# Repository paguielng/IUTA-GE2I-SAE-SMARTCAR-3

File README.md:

# ST STM32: development platform for [PlatformIO](https://platformio.org)

1 Présentation du projet
   ---
1.1 Contexte
   ---
Une entreprise de jouet souhaite développer une voiture pilotée par smartphone, qui intègre plusieurs fonctionnalités comme l'anticollision, le signalement d'obstacle ……

1.2 Objectifs
---
Concevoir, vérifier et valider l'électronique et la programmation d'une voiture pilotée par smartphone afin de :
- Permettre le pilotage de la voiture à partir d'un joystick virtuel sur un smartphone
- Donner, à ce véhicule, de l’autonomie dans certaines prises de décision (anticollision)
- Fournir des informations visuelles et sonores au pilote

1.3 Description de l’existant
---
La voiture est une voiture Radio Commandée déjà existante au catalogue de l'entreprise. Toute l'électronique existante a été supprimée, tout le reste est conservé (carcasse, roues, moteurs, phares …). Les éléments suivants ont été ajoutés à l'intérieur :
- Un module pont en H de référence LF298 pour alimenter le moteur de direction et le moteur de propulsion dans les 2 sens de marche
- Un buzzer passif pour générer un signal avertisseur d'obstacle ou le klaxon
- Deux capteurs infrarouges Sharp de détection d'obstacle
- 6 accumulateurs AA NiMh de 1.2V et 2300mAh en série ou 1 pack batterie de 2 accumulateurs 18650 Li ion de 3.7V de 2600mAh.

1.4 Critères d’acceptabilité du projet
---
Le chef d'entreprise souhaite qu'à la fin de l'étude, lui soient fournis :
- Un dossier de fabrication de la carte électronique (cahier de fabrication + fichiers GERBER + fichier PROTEUS)
- Un dossier technique (cahier de laboratoire + documentation technique + simulations + schémas électriques, schéma d’implantation…)
- Une démonstration avec un prototype opérationnel
- Une étude de coût unitaire pour une production de 100 exemplaires
- Une étude d'autonomie voiture à l’arrêt

2 Expression des besoins
---
2.1 Besoins fonctionnel
---
- Un prototype
- Un dossier technique (cahier de laboratoire)
- Un dossier technique de fabrication (cahier de fabrication ……)
- Une démonstration du système opérationnel

2.2 Fonctionnement global attendu
---
- La voiture est pilotée par smartphone via liaison Bluetooth grâce à un joystick virtuel
- Des dispositifs de sécurité sont mis en œuvre sur la voiture tels que des capteurs de distance d’obstacle avant et arrière, et un avertisseur sonore en fonction de la proximité de l’obstacle.
- L'avertisseur sonore peut être activé directement comme klaxon grâce à un bouton poussoir virtuel sur le smart-phone. Il est aussi possible de générer une mélodie ou des fréquences fixes.
- Un bargraphe virtuel, sur le téléphone, permet d'informer visuellement l'utilisateur de la proximité de l'obstacle à l'avant et/ou du niveau de batterie. (Le niveau de batterie sera indiqué en permanence sauf si proximité d’obs-tacle à l’avant)
- Détection (Près, Moyen et Loin) respectivement moins de 40cm, entre 40 et 60cm et au-delà
- L’utilisateur peut choisir d’activer, de façon permanente, les phares avant et arrière de la voiture grâce à un switch virtuel sur l’écran du smartphone et au besoin de passer dans un mode de gestion automatique grâce à un capteur de luminosité.
- Les phares arrière s’allument plus fort en cas de freinage.
- La température extérieure est reportée sur le smartphone.

2.3 Fonctionnement détaillé attendu
---
- Deux détecteurs de distance infrarouge (un à l’arrière et l’autre à l’avant) permettent de mesurer la distance à l’obstacle et la vitesse d'approche du véhicule, et d’identifier la zone de proximité
- Un buzzer permet d’émettre des bips plus ou moins rapprochés en fonction de la distance à l’obstacle (2 bips par seconde dans la zone Moyen et 4 bips par seconde dans la zone près). Le klaxon est prioritaire sur les bips.
- Le véhicule réduit automatiquement de 50% la consigne de vitesse dans la zone moyenne lorsque le déplace-ment s’effectue vers l’obstacle.
- Le véhicule freine à fond (inversion de la propulsion à consigne maximale), jusqu’à arrêt du véhicule, lorsque le véhicule s’approche de l’obstacle dans la zone près, et cela quel que soit la consigne.
- Les phares arrière s’allument plus fort à chaque freinage.
- Les phares avant et arrière s’allument de façon permanente si le switch virtuel est dans la position “ON” et automatiquement en cas de faible luminosité si le switch est en position “AUTO”
- ,,,,,,,,,,,

3 Contraintes
---
3.1 Coûts
---
Aucune contrainte de coût n’est imposée. En revanche un calcul de coût unitaire pour une production de 100 cartes est attendu (composants électroniques + circuit imprimé + voiture + accessoires + main d'œuvre).

3.2 Autonomie de fonctionnement
---
La voiture doit avoir une autonomie d'au moins 30 minutes avec une batterie de 6 accumulateurs NiMh de capacité 2300mAh.

3.3 Délais de réalisation
---
2h C / 28h TD / 27h TP / 25h autonomie

4 Déroulement du projet
4.1 Séquencement
   ---
- Partie électronique du projet
- Partie Numérique du projet
- Dossier de conception (cahier de laboratoire + documentation technique + simulations)
- Dossier de fabrication (cahier de fabrication + fichiers GERBER + fichier PROTEUS)

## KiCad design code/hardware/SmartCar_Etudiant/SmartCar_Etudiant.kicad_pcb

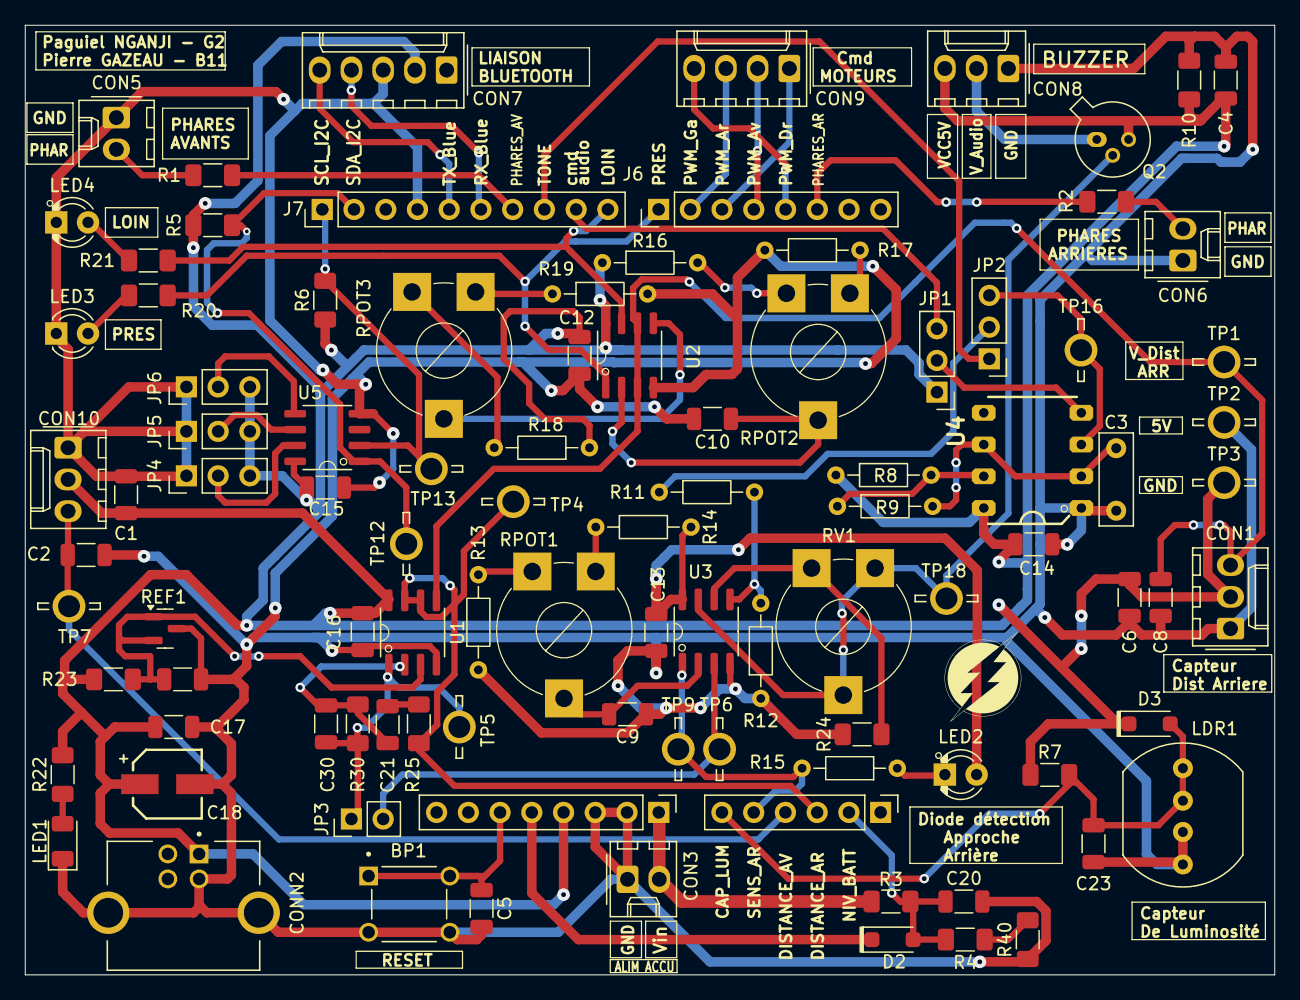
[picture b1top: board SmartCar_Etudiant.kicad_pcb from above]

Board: 2 copper layers, 100.0 x 76.0 mm, 98 parts (0 on the bottom side), 58 nets.

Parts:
BP1: SW_TS02-66-60-BK-260-LCR-D; Button_Reset
C1, C6: 10uF; C_1206_3216Metric
C2, C5, C8, C9, C10, C12, C13, C14, C15, C16, C17, C19, C20, C23: 100n; C_1206_3216Metric
C3: 100n; CAPA_FILM_L7.2mm_W2.5mm_P5.00mm
C4: 22uF; C_1206_3216Metric
C18: 47uF; CAP ELECTROLY CMS 5MM
C21, C30: C_1206_3216Metric
CON1, CON8, CON10: Conn_01x03; Molex_KK-254_AE-6410-03A_1x03_P2.54mm_Vertical
CON3, CON5, CON6: Conn_01x02; Molex_KK-254_AE-6410-02A_1x02_P2.54mm_Vertical
CON7: Conn_01x05; Molex_KK-254_AE-6410-05A_1x05_P2.54mm_Vertical
CON9: Conn_01x04; Molex_KK-254_AE-6410-04A_1x04_P2.54mm_Vertical
CONN2: USB_B
D2, D3: BAT42W-V; D_SOD-123
J4: Conn_Sil_06; PinHeader_1x06_P2.54mm_Vertical
J5, J6: Conn_Sil_08; PinHeader_1x08_P2.54mm_Vertical
J7: Conn_Sil_10; PinHeader_1x10_P2.54mm_Vertical
JP1, JP2: Jumper_3_Bridged12; PinHeader_1x03_P2.54mm_Vertical
JP3: Jumper_2; PinHeader_1x02_P2.54mm_Vertical
JP4, JP5, JP6: Jumper_3; PinHeader_1x03_P2.54mm_Vertical
LDR1: LDR; LDR_11x9.4mm_4.1x3.4mm_Vertical
LED1: LED_BLEU; LED_1206_3216Metric
LED2: LED Orange; LED_D3.0mm_Orange
LED3: LED Rouge; LED_D3.0mm
LED4: LED Verte; LED_D3.0mm_Green
Q2: 2N2222A; TO-18
R1, R2: 220; R_1206_3216Metric_Pad1.30x1.75mm_HandSolder
R3: 5.6k; R_1206_3216Metric_Pad1.30x1.75mm_HandSolder
R4: 3.3k; R_1206_3216Metric_Pad1.30x1.75mm_HandSolder
R5, R6: 10k; R_1206_3216Metric_Pad1.30x1.75mm_HandSolder
R7: 22k; R_1206_3216Metric_Pad1.30x1.75mm_HandSolder
R8, R17, R19: 470; R_Axial_DIN0204_L3.6mm_D1.6mm_P7.62mm_Horizontal
R9: 2.2k; R_Axial_DIN0204_L3.6mm_D1.6mm_P7.62mm_Horizontal
R10: 1M; R_1206_3216Metric_Pad1.30x1.75mm_HandSolder
R11: 10k; R_Axial_DIN0204_L3.6mm_D1.6mm_P7.62mm_Horizontal
R12, R13, R14, R15: 1k; R_Axial_DIN0204_L3.6mm_D1.6mm_P7.62mm_Horizontal
R16, R18: 5.6k; R_Axial_DIN0204_L3.6mm_D1.6mm_P7.62mm_Horizontal
R20, R21, R23: 680; R_1206_3216Metric_Pad1.30x1.75mm_HandSolder
R22: 1k; R_1206_3216Metric_Pad1.30x1.75mm_HandSolder
R24: 2.2k; R_1206_3216Metric_Pad1.30x1.75mm_HandSolder
R25, R30, R40: R_1206_3216Metric_Pad1.30x1.75mm_HandSolder
REF1: ZTL431; SOT-23
RPOT1: 470; Potentiometer standard
RPOT2, RPOT3: 1k; Potentiometer standard
RV1: 47k; Potentiometer standard
TP1, TP2, TP3, TP4, TP5, TP6, TP7, TP9, TP12, TP13, TP16, TP18: TestPoint; PT
U1, U2, U3: MCP6002; SO8_3.9x4.9mm_P1.27mm
U4: NE555D; DIL8
U5: MCP9801_SO8; SO8_3.9x4.9mm_P1.27mm

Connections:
+2V5: C19.1, R23.1, REF1.2 (REF), REF1.3 (K), U1.3
+3.3V: D2.1 (K), J5.5
+5V: C1.2, C4.1, C6.2, C12.1, C13.1, C14.1, C15.1, C16.1, C17.1, C18.1, CON1.2, CON7.2, CON8.3, CON10.2, CONN2.1 (VBUS), D3.1 (K), J5.4, JP1.1 (A), JP4.3 (B), JP5.3 (B), JP6.3 (B), LED2.2 (A), Q2.3 (C1), R5.1, R6.1, R7.1, R8.1, R10.2, R14.2, R16.1, R18.1, R22.2, R23.2, TP3.1 (TP), U1.8, U2.8, U3.8, U4.8 (VCC), U5.8 (V_{DD})
CAP_LUM: C23.1, D3.2 (A), J4.6, LDR1.1, R7.2
CMD_GENE_AUDIO: J7.9, JP1.3 (B)
DISTANCE_AR: J4.3, R25.1, TP4.1 (TP), U1.6, U1.7
DISTANCE_AV: C2.1, CON10.3, J4.4, TP7.1 (TP)
GND: BP1.3, BP1.4, C1.1, C2.2, C3.2, C4.2, C5.2, C6.1, C8.2, C9.2, C10.2, C12.2, C13.2, C14.2, C15.2, C16.2, C17.2, C18.2, C19.2, C20.2, C23.2, CON1.1, CON3.1, CON5.1, CON6.1, CON7.3, CON8.1, CON10.1, CONN2.4 (GND), CONN2.5 (Shield), J5.2, J5.3, J7.4, JP4.1 (A), JP5.1 (A), JP6.1 (A), LDR1.2, LED1.1 (K), LED3.1 (K), LED4.1 (K), R10.1, R12.1, R13.1, R17.2, R19.2, R24.1, R40.1, REF1.1 (A), TP2.1 (TP), U1.4, U2.4, U3.4, U4.1 (GND), U5.4 (GND)
LOIN: J7.10, R21.2, U2.7
NIV_BATT: C20.1, D2.2 (A), J4.2, R3.1, R4.2
unnamed: C9.1, RPOT1.2, U3.2
unnamed: C10.1, RPOT2.2, U2.2
unnamed: RPOT3.2, U2.5
unnamed: C21.1, R25.2
unnamed: C21.2, C30.1, R30.1, U1.2
unnamed: C8.1, CON1.3, TP1.1 (TP), U1.5, U2.3, U2.6
unnamed: CON5.2, R1.1
unnamed: CON6.2, R2.1
unnamed: JP1.2 (C), U4.4 (R)
unnamed: JP2.3 (B), TP16.1 (TP), U4.3 (Q)
unnamed: JP2.2 (C), R11.1
unnamed: C30.2, JP3.1 (A), R30.2, TP5.1 (TP), U1.1
unnamed: JP3.2 (B), TP6.1 (TP), U3.3
unnamed: JP4.2 (C), U5.7 (A0)
unnamed: JP5.2 (C), U5.6 (A1)
unnamed: JP6.2 (C), U5.5 (A2)
unnamed: LED1.2 (A), R22.1
unnamed: LED2.1 (K), R15.1
unnamed: LED3.2 (A), R20.1
unnamed: LED4.2 (A), R21.1
unnamed: Q2.2 (B1), RV1.2, RV1.3, TP18.1 (TP), U3.7
unnamed: R4.1, R40.2
unnamed: R11.2, R12.2, U3.5
unnamed: R13.2, RPOT1.1
unnamed: R14.1, RPOT1.3
unnamed: R16.2, RPOT2.1
unnamed: R17.1, RPOT2.3
unnamed: R18.2, RPOT3.1
unnamed: R19.1, RPOT3.3
unnamed: R24.2, RV1.1, U3.6
unnamed: R8.2, R9.1, U4.7 (DIS)
unnamed: C3.1, R9.2, U4.2 (TR), U4.6 (THR)
PHARES_AR: J6.6, R2.2
PHARES_AV: J7.7, R1.2
PRES: J6.1, R20.2, U2.1
PWM_AR: CON9.1, J6.3
PWM_AV: CON9.2, J6.4
PWM_DROITE: CON9.4, J6.5
PWM_GAUCHE: CON9.3, J6.2
RESET: BP1.1, BP1.2, C5.1, J5.6
RX_BLUETOOTH: CON7.4, J7.6
SCL: J7.1, R6.2, TP13.1 (TP), U5.2 (SCL)
SDA: J7.2, R5.2, TP12.1 (TP), U5.1 (SDA)
SENS_AR: J4.5, R15.2, TP9.1 (TP), U3.1
TONE: J7.8, JP2.1 (A)
TX_BLUETOOTH: CON7.5, J7.5
VIN: CON3.2, J5.1, R3.2
V_AUDIO: CON8.2, Q2.1 (E1)

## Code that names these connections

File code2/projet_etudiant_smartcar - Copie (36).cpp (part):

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///////////////////////////////////////////////////////////
//  Déclarations des ALIAS des broches analogiques (pin) //
///////////////////////////////////////////////////////////
#define CAP_LUM_PIN A0  // le terme CAP_LUM_PIN sera remplacé par le compilateur* par le terme A0 (*par le préprocesseur)
#define SENS_AR_PIN PA1 // changé de A1 à PA1 par Regis Nohe
#define DISTANCE_AV_PIN A2
#define DISTANCE_AR_PIN A3
#define NIV_BATT_PIN A4

///////////////////////////////////////////////
//  Déclarations des ALIAS des broches (pin) //
///////////////////////////////////////////////
const uint32_t PHARES_AR_PIN = D2;
const uint32_t PHARES_AV_PIN = D11;

const uint32_t CMD_GENE_AUDIO_PIN = D9;
const uint32_t TONE_PIN = D10;
const uint32_t PRES_PIN = D7;
const uint32_t LOIN_PIN = D8;

const uint32_t PWM_AVANT_PIN = D4;
const uint32_t PWM_ARRIERE_PIN = D5;
const uint32_t PWM_DROITE_PIN = D3;
const uint32_t PWM_GAUCHE_PIN = D6;

const uint16_t RX_PIN = D12; // mettre à jour les #define des codes générés par RemoteXY
const uint16_t TX_PIN = D13; // mettre à jour les #define des codes générés par RemoteXY
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  else if (cap_av > limite_superieur)
  {
    // RemoteXY.Bargraph = 100; // Barre plein
    int nivBat = analogRead(NIV_BATT_PIN); // NIV_BATT_PIN prend automatiquement la broche associé (A4)
    gestion_bargraphe(nivB);
  }
  else
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
  if (phareAv)
  {
    digitalWrite(PHARES_AV_PIN, HIGH);
  }
  else
    digitalWrite(PHARES_AV_PIN, LOW);
}

////////////////////////////////////////////////////
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      }
    }
  }
  digitalWrite(CMD_GENE_AUDIO_PIN, buzzerState);
}

////////////////////////////////////////////////////
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    }
  }

  digitalWrite(CMD_GENE_AUDIO_PIN, buzzerState);
}

////////////////////////////////////////////
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  /////////////////////////////////////////////////////////////////////
  // Initialisation des broches en entrée ou en sortie               //
  /////////////////////////////////////////////////////////////////////
  pinMode(CMD_GENE_AUDIO_PIN, OUTPUT); // CMD_GENE_AUDIO_PIN est configurée en sortie
  pinMode(PRES_PIN, INPUT);            // PRES_PIN est configurée en sortie
  pinMode(LOIN_PIN, INPUT);            // LOIN_PIN est configurée en sortie
  pinMode(SENS_AR_PIN, INPUT);         // SENS_AR_PIN est configurée en sortie
  pinMode(PHARES_AV_PIN, OUTPUT);

  /////////////////////////////////////////////////////////////////////
  // Initialisation des timer PWM Direction                          //
  /////////////////////////////////////////////////////////////////////

  timerDirection.setMode(CANAL_DROITE, TIMER_OUTPUT_COMPARE_PWM1, PWM_DROITE_PIN);
  timerDirection.setMode(CANAL_GAUCHE, TIMER_OUTPUT_COMPARE_PWM1, PWM_GAUCHE_PIN);
  timerDirection.setPrescaleFactor(44);
  timerDirection.setOverflow(100);
  timerDirection.setCaptureCompare(CANAL_DROITE, 0);
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  // timerPhares.setPrescaleFactor(1600); // calculé en TD
  // timerPhares.setOverflow(100);

  // timerPhares.setMode(CANAL_PHARE, TIMER_OUTPUT_COMPARE_PWM1, PHARES_AR_PIN);
  // timerPhares.setCaptureCompare(CANAL_PHARE, 0);

  // timerPhares.resume();
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  ///////////////////////////////////////
  //  Informations de l'environnement  //
  ///////////////////////////////////////
  pres = digitalRead(PRES_PIN);      // Présence d'un obstacle à moins de 40cm (pres = '1')
  loin = digitalRead(LOIN_PIN);      // Présence d'un obstacle à plus de 40cm (LOIN = '10')
  nivBat = analogRead(NIV_BATT_PIN); // NIV_BATT_PIN prend automatiquement la broche associé (A4)
  capt_av = analogRead(DISTANCE_AV_PIN);
  sens_ar = digitalRead(SENS_AR_PIN);
  cap_lum = analogRead(CAP_LUM_PIN);
  cap_avant = analogRead(DISTANCE_AV_PIN);

  //////////////////////////////////////
  //  Jeu de test pour gestio_buzzer  //
  //////////////////////////////////////
  loin = 1;
  pres = 0;
  RemoteXY.klaxon = 0;

  ///////////////////////////////
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
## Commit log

2026-05-30 Ajout des dossiers code, hardware et docs
2026-05-30 Rename main_etudiant_vide.cpp to etudiant_vide.cpp
2026-05-30 Rename etudiant_vide.cpp to fichier_etudiant_vide.cpp
2026-05-30 Rename fichier_etudiant_vide.cpp to main.cpp
2026-05-31 Rename Réalisation de la carte shield DELANNEEDERNIERE.pdf to Réalisation de la carte shield.pdf
2026-05-31 Rename Présentation de la SAE1_S2.pdf to Présentation_de_la_SAE1_S2.pdf
2026-05-31 Remove document overview and add PDF badge
2026-05-31 Rename Présentation_de_la_SAE1_S2.pdf to Présentation de la SAE1 S2.pdf
2026-05-31 Create 1
2026-05-31 Rename images/373f4a1e-5e04-4d97-9719-7f8ffd22365d.png to TestOffice/images/373f4a1e-5e04-4d97-9719-7f8ffd22365d.png
2026-05-31 Rename TestOffice/images/373f4a1e-5e04-4d97-9719-7f8ffd22365d.png to TestOffice/TestOffice/images/373f4a1e-5e04-4d97-9719-7f8ffd22365d.png
2026-05-31 Rename images/e6b50829-5484-4663-ac60-6074ad16a8f9.png to TestOffice/images/e6b50829-5484-4663-ac60-6074ad16a8f9.png
2026-05-31 Rename TestOffice/TestOffice/images/373f4a1e-5e04-4d97-9719-7f8ffd22365d.png to TestOffice/images/373f4a1e-5e04-4d97-9719-7f8ffd22365d.png
2026-05-31 Rename Office2Md.md to README.md
2026-05-31 Rename README.md to Office2Md.md
2026-05-31 Rename README2.md to README.md
2026-06-10 Rename README (1).rst to README.rst
2026-06-10 Rename README (2).md to README.md
